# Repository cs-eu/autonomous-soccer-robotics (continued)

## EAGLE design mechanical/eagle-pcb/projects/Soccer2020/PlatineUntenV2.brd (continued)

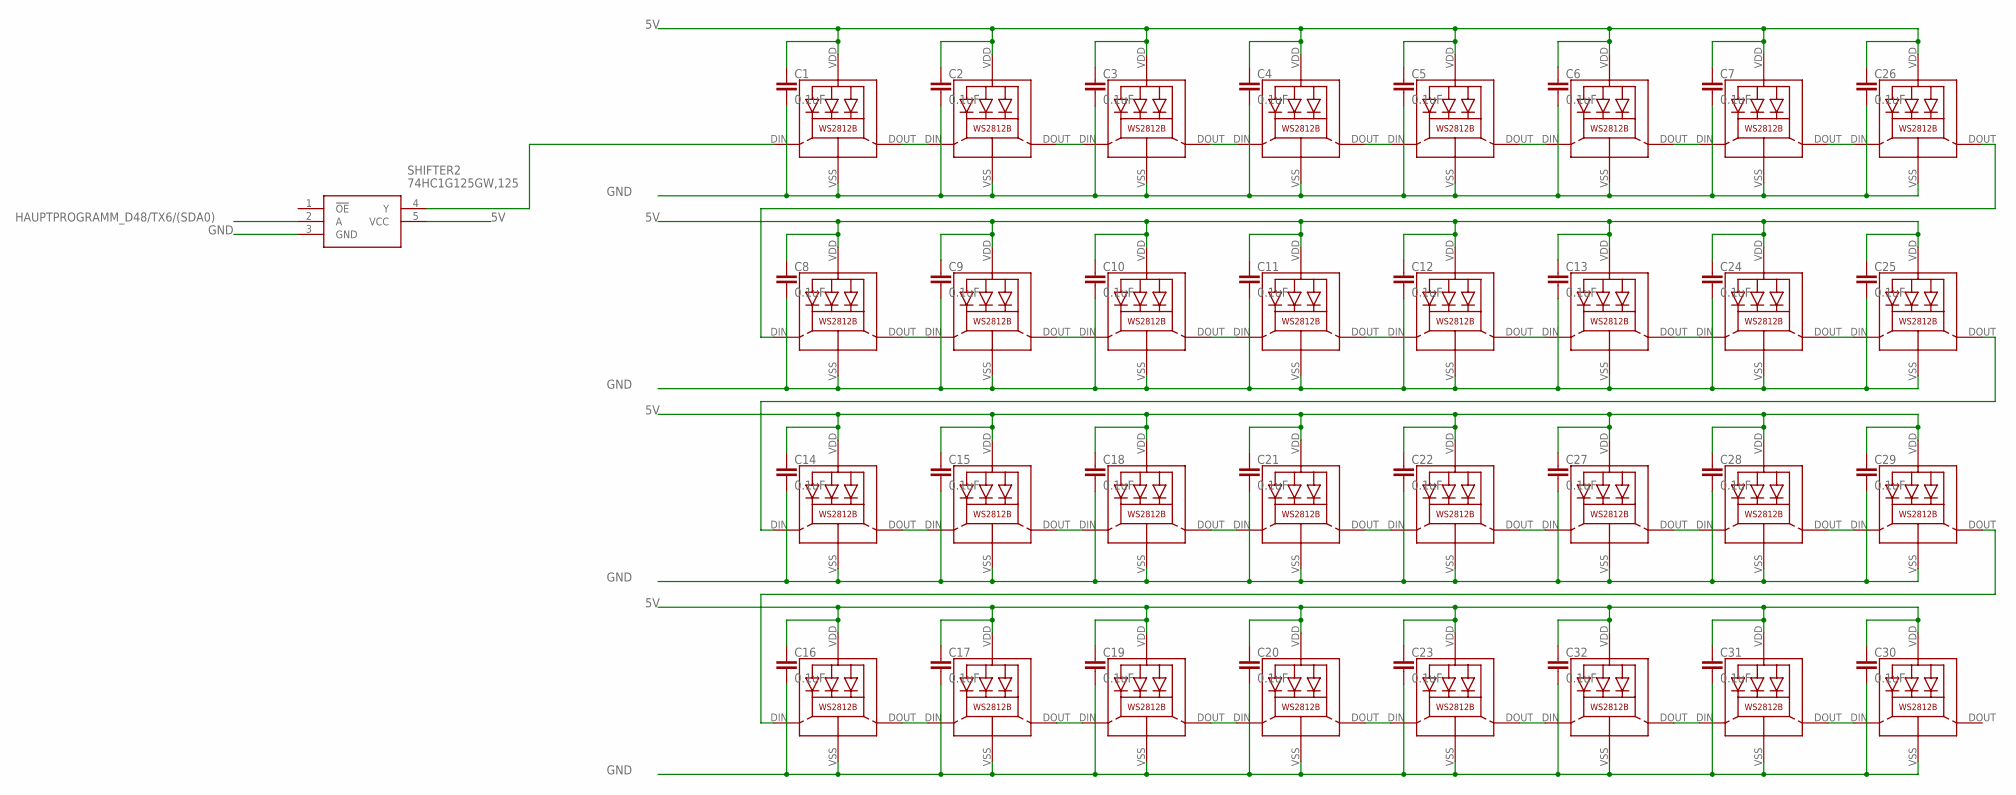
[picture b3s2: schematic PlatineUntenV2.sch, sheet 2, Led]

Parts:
C1, C2, C3, C4, C5, C6, C7, C8, C9, C10, C11, C12, C13, C14, C15, C16, C17, C18, C19, C20, C21, C22, C23, C24, C25, C26, C27, C28, C29, C30, C31, C32: 0.1uF; C0805
LED33, LED34, LED35, LED36, LED37, LED38, LED39, LED40, LED41, LED42, LED43, LED44, LED45, LED46, LED47, LED48, LED49, LED50, LED51, LED52, LED53, LED54, LED55, LED56, LED57, LED58, LED59, LED60, LED61, LED62, LED63, LED64: WS2812B
SHIFTER2: 74HC1G125GW,125; SOT65P212X110-5N

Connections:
5V: C1.1, C2.1, C3.1, C4.1, C5.1, C6.1, C7.1, C8.1, C9.1, C10.1, C11.1, C12.1, C13.1, C14.1, C15.1, C16.1, C17.1, C18.1, C19.1, C20.1, C21.1, C22.1, C23.1, C24.1, C25.1, C26.1, C27.1, C28.1, C29.1, C30.1, C31.1, C32.1, LED33.VDD, LED34.VDD, LED35.VDD, LED36.VDD, LED37.VDD, LED38.VDD, LED39.VDD, LED40.VDD, LED41.VDD, LED42.VDD, LED43.VDD, LED44.VDD, LED45.VDD, LED46.VDD, LED47.VDD, LED48.VDD, LED49.VDD, LED50.VDD, LED51.VDD, LED52.VDD, LED53.VDD, LED54.VDD, LED55.VDD, LED56.VDD, LED57.VDD, LED58.VDD, LED59.VDD, LED60.VDD, LED61.VDD, LED62.VDD, LED63.VDD, LED64.VDD, SHIFTER2.5 (VCC); also elsewhere on the board
GND: C1.2, C2.2, C3.2, C4.2, C5.2, C6.2, C7.2, C8.2, C9.2, C10.2, C11.2, C12.2, C13.2, C14.2, C15.2, C16.2, C17.2, C18.2, C19.2, C20.2, C21.2, C22.2, C23.2, C24.2, C25.2, C26.2, C27.2, C28.2, C29.2, C30.2, C31.2, C32.2, LED33.VSS (GND), LED34.VSS (GND), LED35.VSS (GND), LED36.VSS (GND), LED37.VSS (GND), LED38.VSS (GND), LED39.VSS (GND), LED40.VSS (GND), LED41.VSS (GND), LED42.VSS (GND), LED43.VSS (GND), LED44.VSS (GND), LED45.VSS (GND), LED46.VSS (GND), LED47.VSS (GND), LED48.VSS (GND), LED49.VSS (GND), LED50.VSS (GND), LED51.VSS (GND), LED52.VSS (GND), LED53.VSS (GND), LED54.VSS (GND), LED55.VSS (GND), LED56.VSS (GND), LED57.VSS (GND), LED58.VSS (GND), LED59.VSS (GND), LED60.VSS (GND), LED61.VSS (GND), LED62.VSS (GND), LED63.VSS (GND), LED64.VSS (GND), SHIFTER2.3 (GND); also elsewhere on the board
HAUPTPROGRAMM_D48/TX6/(SDA0): SHIFTER2.2 (A); also elsewhere on the board
unnamed: LED33.DIN (DI), SHIFTER2.4 (Y)
unnamed: LED33.DOUT (DO), LED34.DIN (DI)
unnamed: LED34.DOUT (DO), LED35.DIN (DI)
unnamed: LED35.DOUT (DO), LED36.DIN (DI)
unnamed: LED36.DOUT (DO), LED37.DIN (DI)
unnamed: LED37.DOUT (DO), LED38.DIN (DI)
unnamed: LED38.DOUT (DO), LED39.DIN (DI)
unnamed: LED39.DOUT (DO), LED40.DIN (DI)
unnamed: LED40.DOUT (DO), LED41.DIN (DI)
unnamed: LED41.DOUT (DO), LED42.DIN (DI)
unnamed: LED42.DOUT (DO), LED43.DIN (DI)
unnamed: LED43.DOUT (DO), LED44.DIN (DI)
unnamed: LED44.DOUT (DO), LED45.DIN (DI)
unnamed: LED45.DOUT (DO), LED46.DIN (DI)
unnamed: LED46.DOUT (DO), LED47.DIN (DI)
unnamed: LED47.DOUT (DO), LED48.DIN (DI)
unnamed: LED48.DOUT (DO), LED49.DIN (DI)
unnamed: LED49.DOUT (DO), LED50.DIN (DI)
unnamed: LED50.DOUT (DO), LED51.DIN (DI)
unnamed: LED51.DOUT (DO), LED52.DIN (DI)
unnamed: LED52.DOUT (DO), LED53.DIN (DI)
unnamed: LED53.DOUT (DO), LED54.DIN (DI)
unnamed: LED54.DOUT (DO), LED55.DIN (DI)
unnamed: LED55.DOUT (DO), LED56.DIN (DI)
unnamed: LED56.DOUT (DO), LED57.DIN (DI)
unnamed: LED57.DOUT (DO), LED58.DIN (DI)
unnamed: LED58.DOUT (DO), LED59.DIN (DI)
unnamed: LED59.DOUT (DO), LED60.DIN (DI)
unnamed: LED60.DOUT (DO), LED61.DIN (DI)
unnamed: LED61.DOUT (DO), LED62.DIN (DI)
unnamed: LED62.DOUT (DO), LED63.DIN (DI)
unnamed: LED63.DOUT (DO), LED64.DIN (DI)

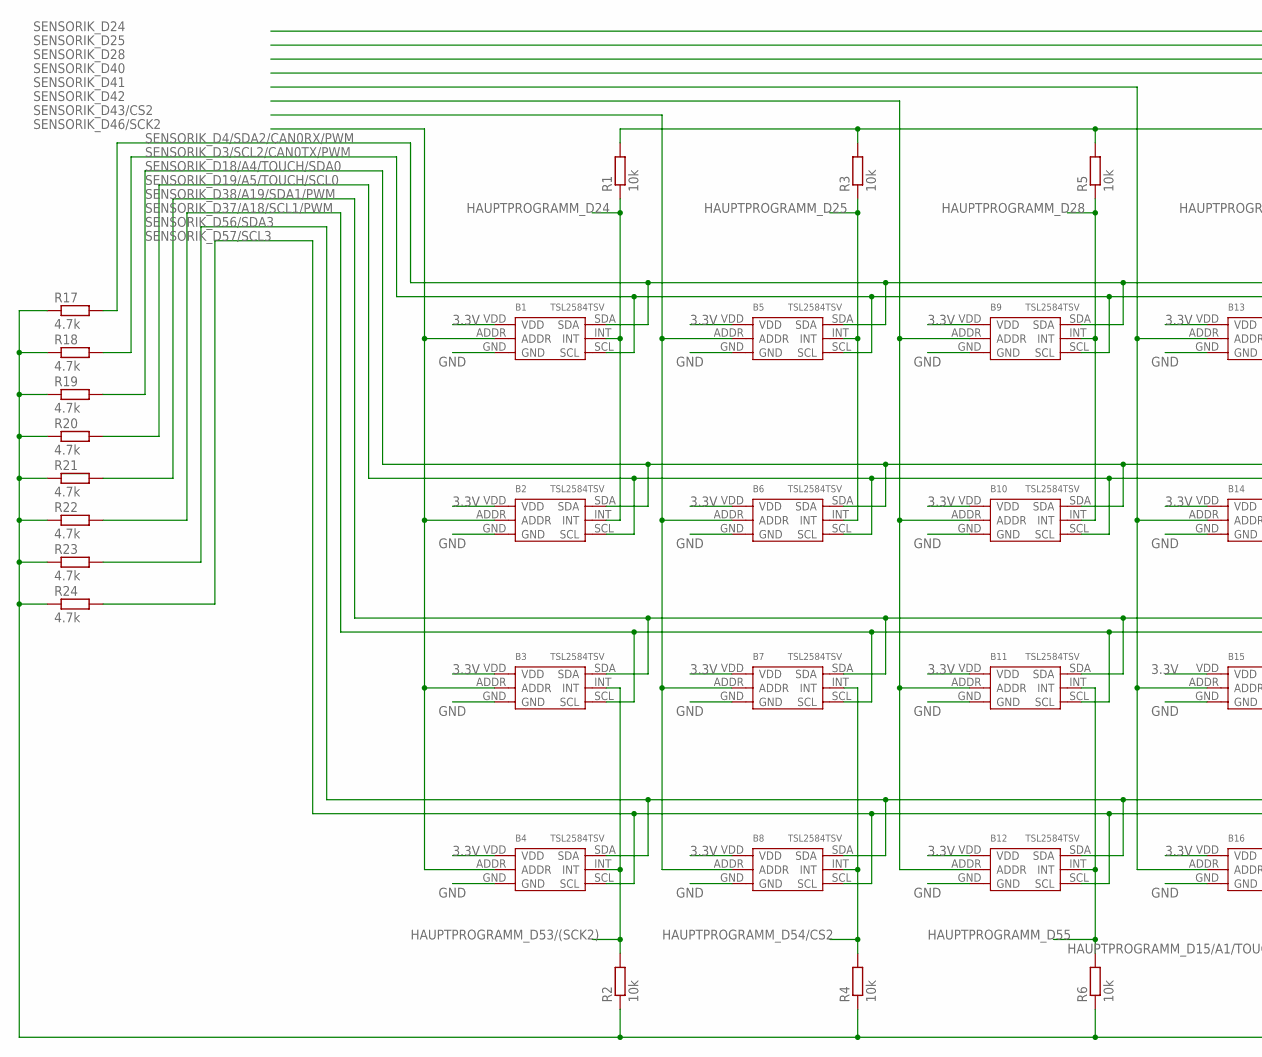
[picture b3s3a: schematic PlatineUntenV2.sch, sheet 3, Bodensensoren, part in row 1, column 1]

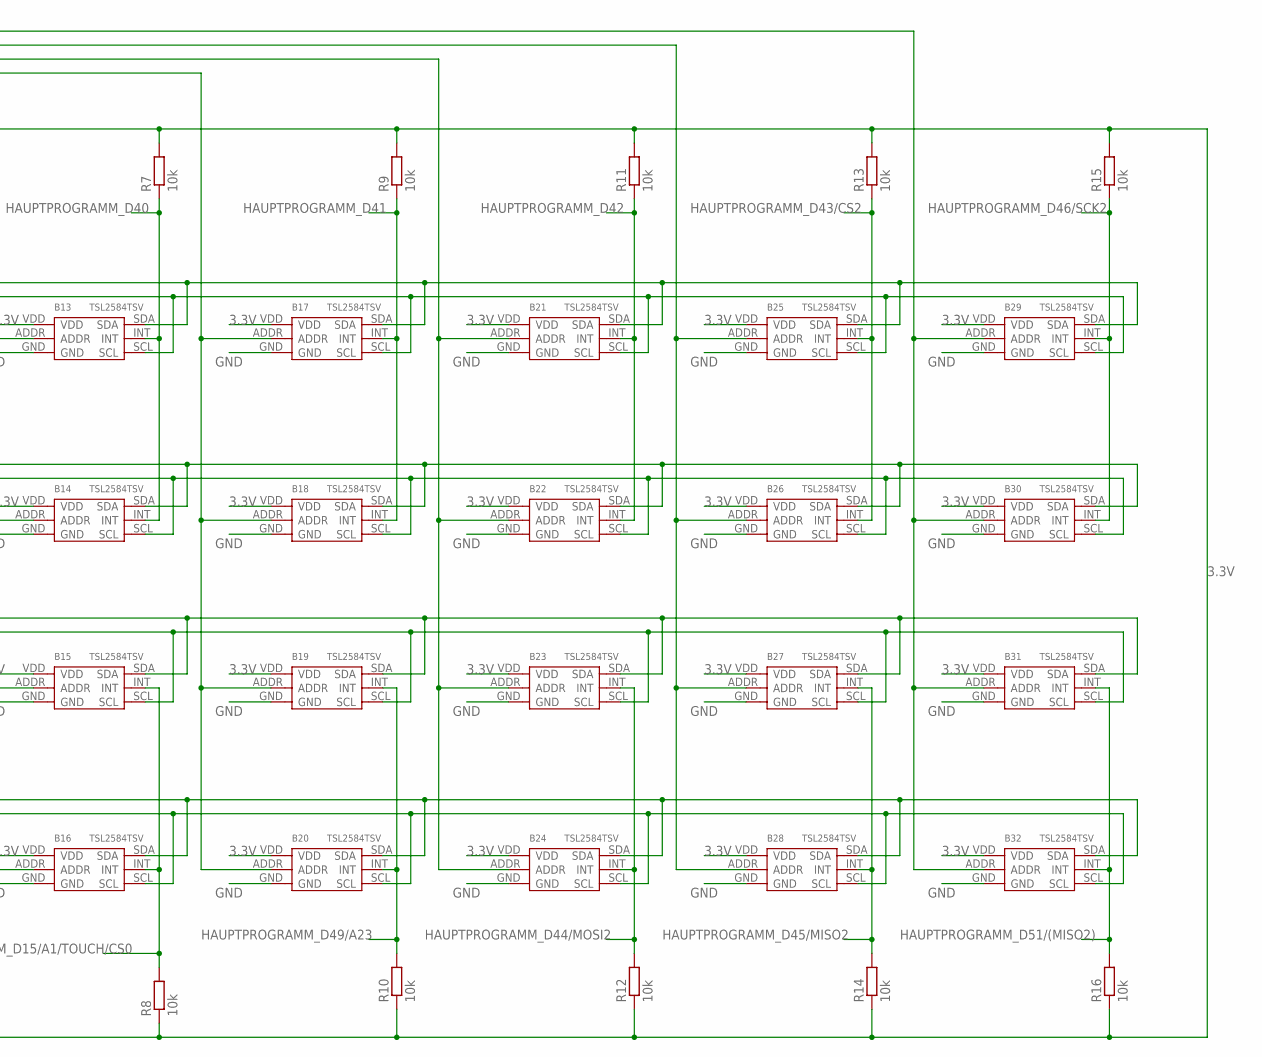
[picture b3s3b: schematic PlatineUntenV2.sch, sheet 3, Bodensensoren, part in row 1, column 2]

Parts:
B1, B2, B3, B4, B5, B6, B7, B8, B9, B10, B11, B12, B13, B14, B15, B16, B17, B18, B19, B20, B21, B22, B23, B24, B25, B26, B27, B28, B29, B30, B31, B32: TSL2584TSV
R1, R2, R3, R4, R5, R6, R7, R8, R9, R10, R11, R12, R13, R14, R15, R16: 10k; R0805
R17, R18, R19, R20, R21, R22, R23, R24: 4.7k; R0805

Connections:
3.3V: B1.VDD, B2.VDD, B3.VDD, B4.VDD, B5.VDD, B6.VDD, B7.VDD, B8.VDD, B9.VDD, B10.VDD, B11.VDD, B12.VDD, B13.VDD, B14.VDD, B15.VDD, B16.VDD, B17.VDD, B18.VDD, B19.VDD, B20.VDD, B21.VDD, B22.VDD, B23.VDD, B24.VDD, B25.VDD, B26.VDD, B27.VDD, B28.VDD, B29.VDD, B30.VDD, B31.VDD, B32.VDD, R1.2, R2.1, R3.2, R4.1, R5.2, R6.1, R7.2, R8.1, R9.2, R10.1, R11.2, R12.1, R13.2, R14.1, R15.2, R16.1, R17.1, R18.1, R19.1, R20.1, R21.1, R22.1, R23.1, R24.1; also elsewhere on the board
GND: B1.GND, B2.GND, B3.GND, B4.GND, B5.GND, B6.GND, B7.GND, B8.GND, B9.GND, B10.GND, B11.GND, B12.GND, B13.GND, B14.GND, B15.GND, B16.GND, B17.GND, B18.GND, B19.GND, B20.GND, B21.GND, B22.GND, B23.GND, B24.GND, B25.GND, B26.GND, B27.GND, B28.GND, B29.GND, B30.GND, B31.GND, B32.GND; also elsewhere on the board
HAUPTPROGRAMM_D15/A1/TOUCH/CS0: B15.INT, B16.INT, R8.2; also elsewhere on the board
HAUPTPROGRAMM_D24: B1.INT, B2.INT, R1.1; also elsewhere on the board
HAUPTPROGRAMM_D25: B5.INT, B6.INT, R3.1; also elsewhere on the board
HAUPTPROGRAMM_D28: B9.INT, B10.INT, R5.1; also elsewhere on the board
HAUPTPROGRAMM_D40: B13.INT, B14.INT, R7.1; also elsewhere on the board
HAUPTPROGRAMM_D41: B17.INT, B18.INT, R9.1; also elsewhere on the board
HAUPTPROGRAMM_D42: B21.INT, B22.INT, R11.1; also elsewhere on the board
HAUPTPROGRAMM_D43/CS2: B25.INT, B26.INT, R13.1; also elsewhere on the board
HAUPTPROGRAMM_D44/MOSI2: B23.INT, B24.INT, R12.2; also elsewhere on the board
HAUPTPROGRAMM_D45/MISO2: B27.INT, B28.INT, R14.2; also elsewhere on the board
HAUPTPROGRAMM_D46/SCK2: B29.INT, B30.INT, R15.1; also elsewhere on the board
HAUPTPROGRAMM_D49/A23: B19.INT, B20.INT, R10.2; also elsewhere on the board
HAUPTPROGRAMM_D51/(MISO2): B31.INT, B32.INT, R16.2; also elsewhere on the board
HAUPTPROGRAMM_D53/(SCK2): B3.INT, B4.INT, R2.2; also elsewhere on the board
HAUPTPROGRAMM_D54/CS2: B7.INT, B8.INT, R4.2; also elsewhere on the board
HAUPTPROGRAMM_D55: B11.INT, B12.INT, R6.2; also elsewhere on the board
SENSORIK_D3/SCL2/CAN0TX/PWM: B1.SCL, B5.SCL, B9.SCL, B13.SCL, B17.SCL, B21.SCL, B25.SCL, B29.SCL, R18.2; also elsewhere on the board
SENSORIK_D4/SDA2/CAN0RX/PWM: B1.SDA, B5.SDA, B9.SDA, B13.SDA, B17.SDA, B21.SDA, B25.SDA, B29.SDA, R17.2; also elsewhere on the board
SENSORIK_D18/A4/TOUCH/SDA0: B2.SDA, B6.SDA, B10.SDA, B14.SDA, B18.SDA, B22.SDA, B26.SDA, B30.SDA, R19.2; also elsewhere on the board
SENSORIK_D19/A5/TOUCH/SCL0: B2.SCL, B6.SCL, B10.SCL, B14.SCL, B18.SCL, B22.SCL, B26.SCL, B30.SCL, R20.2; also elsewhere on the board
SENSORIK_D24: B29.ADDR, B30.ADDR, B31.ADDR, B32.ADDR; also elsewhere on the board
SENSORIK_D25: B25.ADDR, B26.ADDR, B27.ADDR, B28.ADDR; also elsewhere on the board
SENSORIK_D28: B21.ADDR, B22.ADDR, B23.ADDR, B24.ADDR; also elsewhere on the board
SENSORIK_D37/A18/SCL1/PWM: B3.SCL, B7.SCL, B11.SCL, B15.SCL, B19.SCL, B23.SCL, B27.SCL, B31.SCL, R22.2; also elsewhere on the board
SENSORIK_D38/A19/SDA1/PWM: B3.SDA, B7.SDA, B11.SDA, B15.SDA, B19.SDA, B23.SDA, B27.SDA, B31.SDA, R21.2; also elsewhere on the board
SENSORIK_D40: B17.ADDR, B18.ADDR, B19.ADDR, B20.ADDR; also elsewhere on the board
SENSORIK_D41: B13.ADDR, B14.ADDR, B15.ADDR, B16.ADDR; also elsewhere on the board
SENSORIK_D42: B9.ADDR, B10.ADDR, B11.ADDR, B12.ADDR; also elsewhere on the board
SENSORIK_D43/CS2: B5.ADDR, B6.ADDR, B7.ADDR, B8.ADDR; also elsewhere on the board
SENSORIK_D46/SCK2: B1.ADDR, B2.ADDR, B3.ADDR, B4.ADDR; also elsewhere on the board
SENSORIK_D56/SDA3: B4.SDA, B8.SDA, B12.SDA, B16.SDA, B20.SDA, B24.SDA, B28.SDA, B32.SDA, R23.2; also elsewhere on the board
SENSORIK_D57/SCL3: B4.SCL, B8.SCL, B12.SCL, B16.SCL, B20.SCL, B24.SCL, B28.SCL, B32.SCL, R24.2; also elsewhere on the board

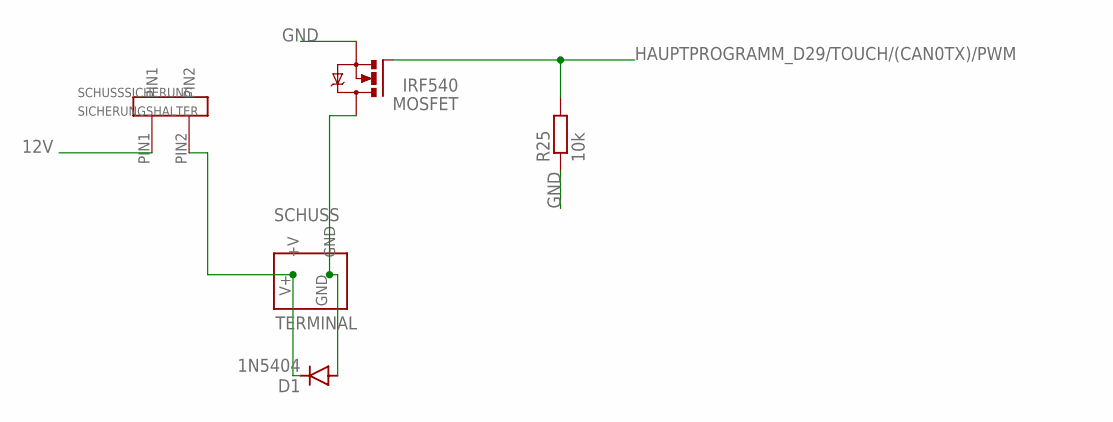
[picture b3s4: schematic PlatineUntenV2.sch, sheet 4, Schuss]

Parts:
D1: 1N5404; DO201-15
MOSFET: IRF540; TO220BV
R25: 10k; R0805
SCHUSS: TERMINAL
SCHUSSSICHERUNG: SICHERUNGSHALTER

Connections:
12V: SCHUSSSICHERUNG.PIN1; also elsewhere on the board
GND: MOSFET.S, R25.1; also elsewhere on the board
HAUPTPROGRAMM_D29/TOUCH/(CAN0TX)/PWM: MOSFET.G, R25.2; also elsewhere on the board
unnamed: D1.A, MOSFET.D, SCHUSS.GND
unnamed: D1.C, SCHUSS.V+ (+V), SCHUSSSICHERUNG.PIN2

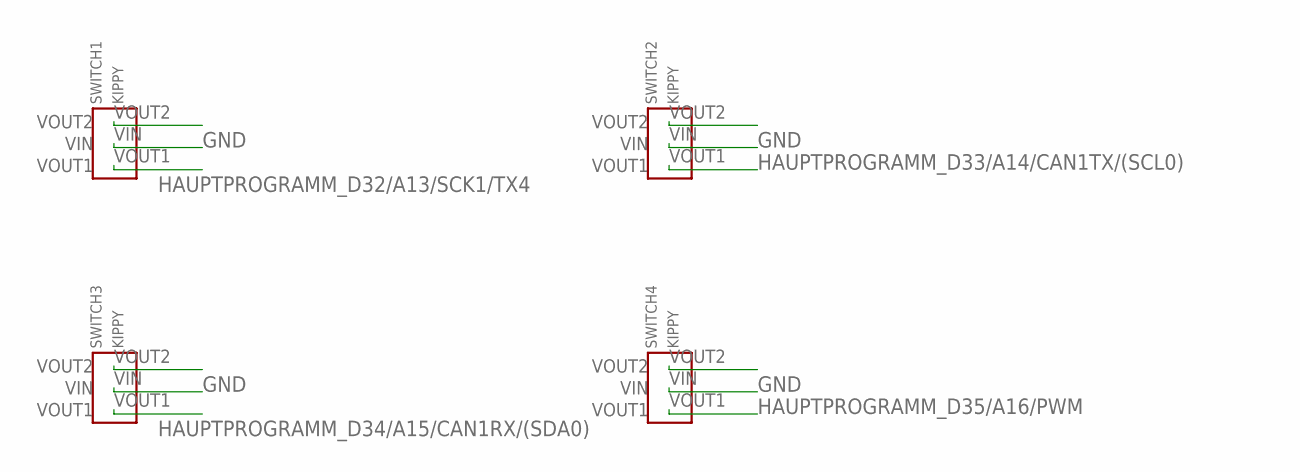
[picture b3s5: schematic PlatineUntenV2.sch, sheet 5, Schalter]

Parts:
SWITCH1, SWITCH2, SWITCH3, SWITCH4: KIPPY

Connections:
GND: SWITCH1.VIN, SWITCH2.VIN, SWITCH3.VIN, SWITCH4.VIN; also elsewhere on the board
HAUPTPROGRAMM_D32/A13/SCK1/TX4: SWITCH1.VOUT1; also elsewhere on the board
HAUPTPROGRAMM_D33/A14/CAN1TX/(SCL0): SWITCH2.VOUT1; also elsewhere on the board
HAUPTPROGRAMM_D34/A15/CAN1RX/(SDA0): SWITCH3.VOUT1; also elsewhere on the board
HAUPTPROGRAMM_D35/A16/PWM: SWITCH4.VOUT1; also elsewhere on the board

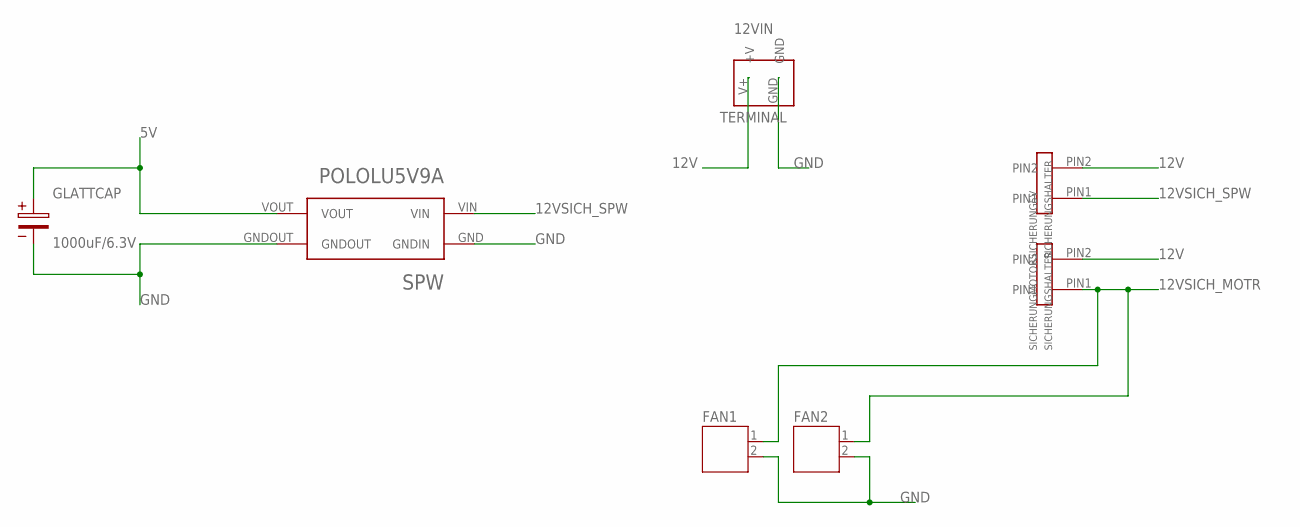
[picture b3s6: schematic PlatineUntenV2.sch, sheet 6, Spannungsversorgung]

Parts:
12VIN: TERMINAL
FAN1, FAN2: JST-PH2
GLATTCAP: 1000uF/6.3V; GLATTCAP
SICHERUNG5V: SICHERUNGSHALTER
SICHERUNGMOTOR: SICHERUNGSHALTER
SPW: POLOLU5V9A

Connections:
5V: GLATTCAP.1, SPW.VOUT; also elsewhere on the board
12V: 12VIN.V+ (+V), SICHERUNG5V.PIN2, SICHERUNGMOTOR.PIN2; also elsewhere on the board
12VSICH_MOTR: FAN1.1, FAN2.1, SICHERUNGMOTOR.PIN1; also elsewhere on the board
12VSICH_SPW: SICHERUNG5V.PIN1, SPW.VIN
GND: 12VIN.GND, FAN1.2, FAN2.2, GLATTCAP.2, SPW.GND (GNDIN), SPW.GNDOUT; also elsewhere on the board

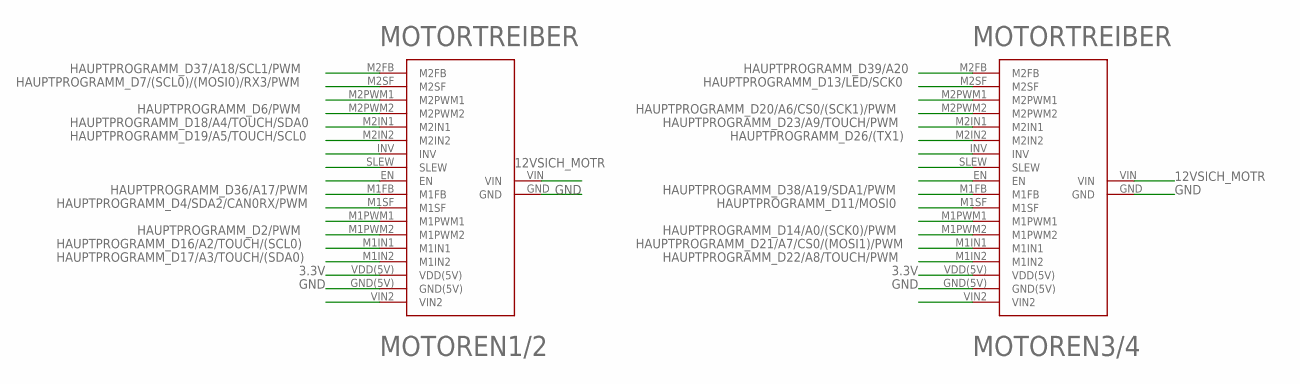
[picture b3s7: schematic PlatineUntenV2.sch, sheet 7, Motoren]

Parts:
MOTOREN1/2, MOTOREN3/4: MOTORTREIBER

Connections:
3.3V: MOTOREN1/2.VDD(5V), MOTOREN3/4.VDD(5V); also elsewhere on the board
12VSICH_MOTR: MOTOREN1/2.VIN, MOTOREN3/4.VIN; also elsewhere on the board
GND: MOTOREN1/2.GND, MOTOREN1/2.GND(5V), MOTOREN3/4.GND, MOTOREN3/4.GND(5V); also elsewhere on the board
HAUPTPROGRAMM_D2/PWM: MOTOREN1/2.M1PWM2; also elsewhere on the board
HAUPTPROGRAMM_D4/SDA2/CAN0RX/PWM: MOTOREN1/2.M1SF; also elsewhere on the board
HAUPTPROGRAMM_D6/PWM: MOTOREN1/2.M2PWM2; also elsewhere on the board
HAUPTPROGRAMM_D7/(SCL0)/(MOSI0)/RX3/PWM: MOTOREN1/2.M2SF; also elsewhere on the board
HAUPTPROGRAMM_D11/MOSI0: MOTOREN3/4.M1SF; also elsewhere on the board
HAUPTPROGRAMM_D13/LED/SCK0: MOTOREN3/4.M2SF; also elsewhere on the board
HAUPTPROGRAMM_D14/A0/(SCK0)/PWM: MOTOREN3/4.M1PWM2; also elsewhere on the board
HAUPTPROGRAMM_D16/A2/TOUCH/(SCL0): MOTOREN1/2.M1IN1; also elsewhere on the board
HAUPTPROGRAMM_D17/A3/TOUCH/(SDA0): MOTOREN1/2.M1IN2; also elsewhere on the board
HAUPTPROGRAMM_D18/A4/TOUCH/SDA0: MOTOREN1/2.M2IN1; also elsewhere on the board
HAUPTPROGRAMM_D19/A5/TOUCH/SCL0: MOTOREN1/2.M2IN2; also elsewhere on the board
HAUPTPROGRAMM_D20/A6/CS0/(SCK1)/PWM: MOTOREN3/4.M2PWM2; also elsewhere on the board
HAUPTPROGRAMM_D21/A7/CS0/(MOSI1)/PWM: MOTOREN3/4.M1IN1; also elsewhere on the board
HAUPTPROGRAMM_D22/A8/TOUCH/PWM: MOTOREN3/4.M1IN2; also elsewhere on the board
HAUPTPROGRAMM_D23/A9/TOUCH/PWM: MOTOREN3/4.M2IN1; also elsewhere on the board
HAUPTPROGRAMM_D26/(TX1): MOTOREN3/4.M2IN2; also elsewhere on the board
HAUPTPROGRAMM_D36/A17/PWM: MOTOREN1/2.M1FB; also elsewhere on the board
HAUPTPROGRAMM_D37/A18/SCL1/PWM: MOTOREN1/2.M2FB; also elsewhere on the board
HAUPTPROGRAMM_D38/A19/SDA1/PWM: MOTOREN3/4.M1FB; also elsewhere on the board
HAUPTPROGRAMM_D39/A20: MOTOREN3/4.M2FB; also elsewhere on the board

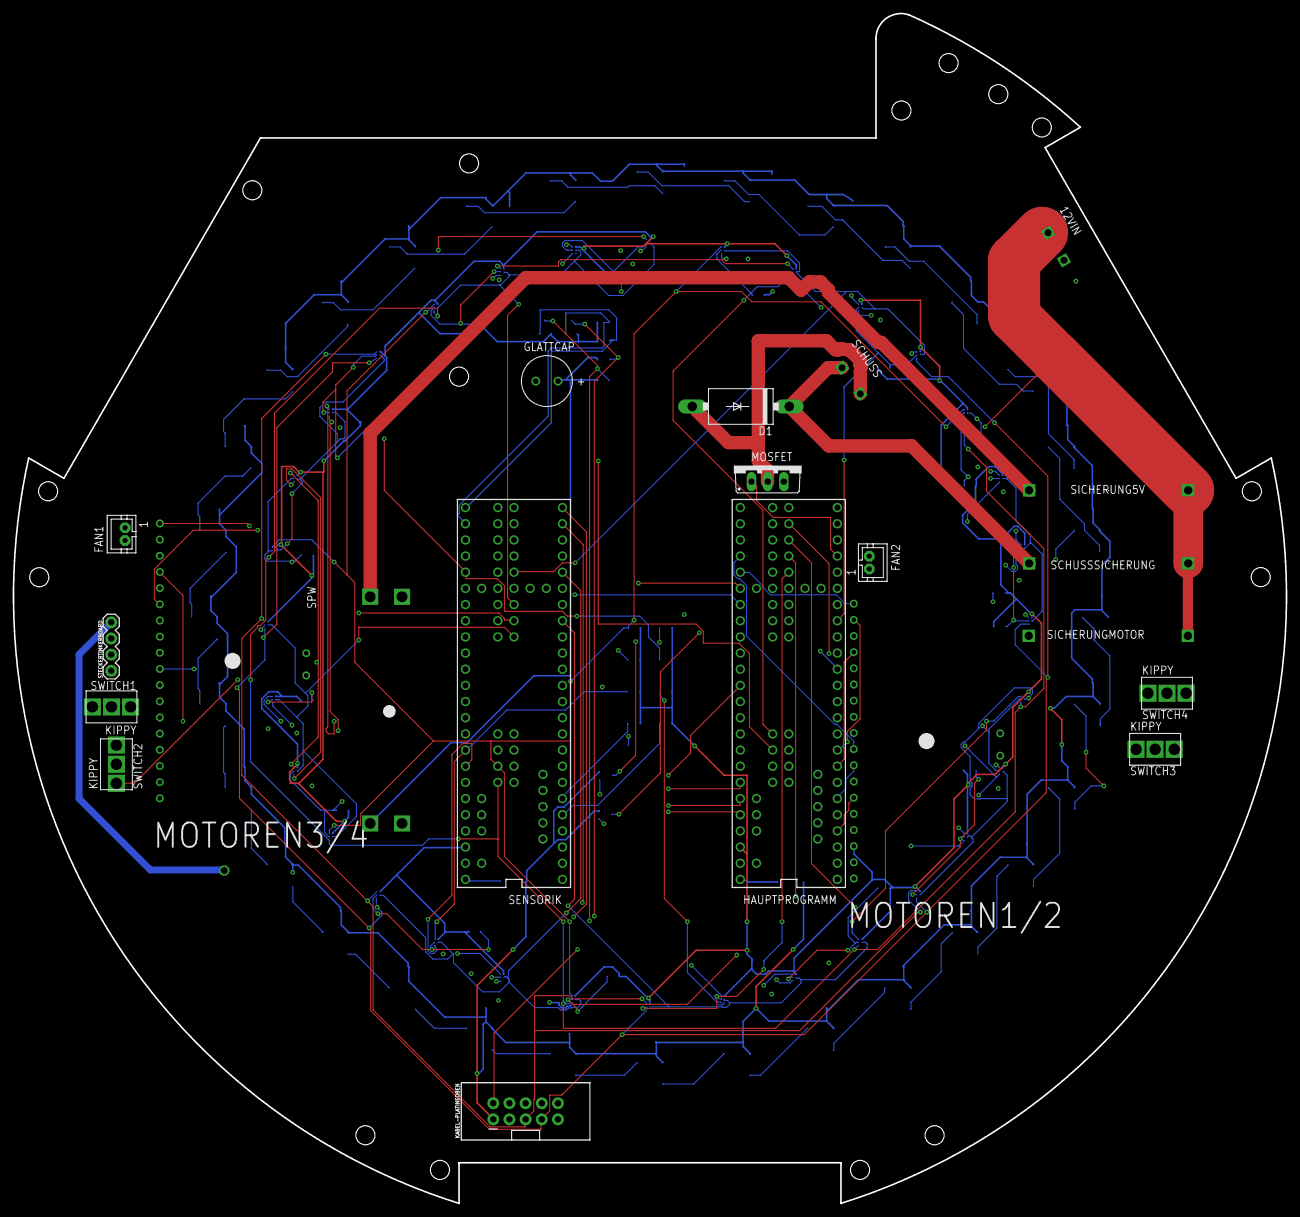
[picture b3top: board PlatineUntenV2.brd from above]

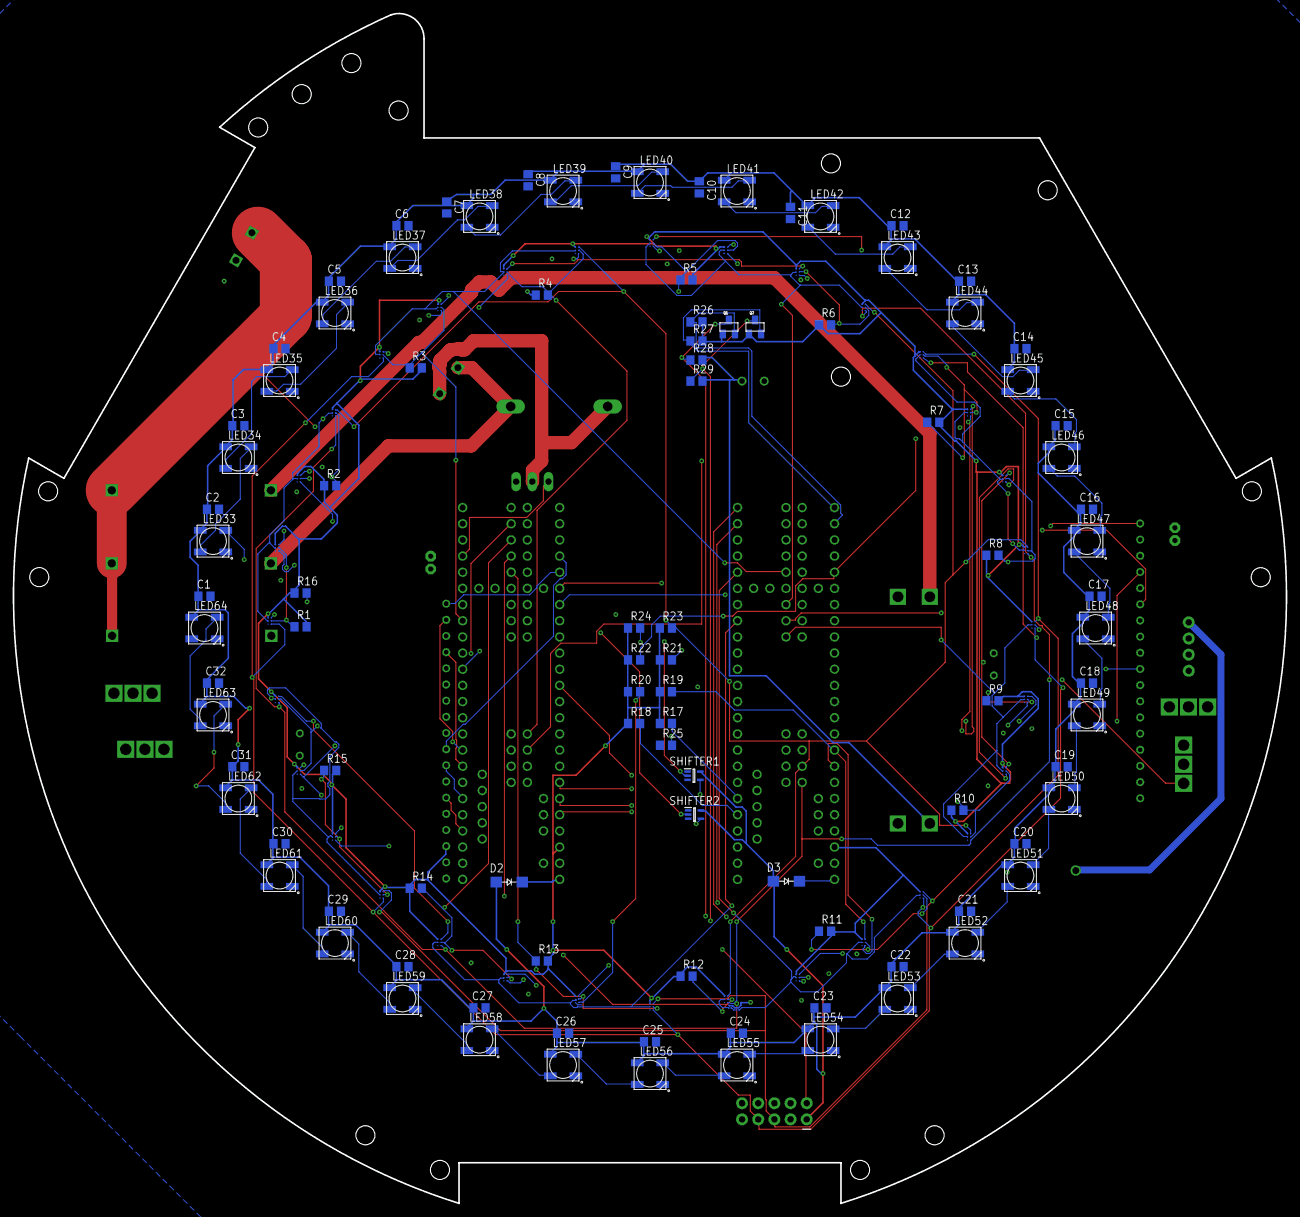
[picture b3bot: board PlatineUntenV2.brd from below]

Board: 4 copper layers, 200.0 x 186.9 mm, 152 parts (131 on the bottom side), 113 nets.

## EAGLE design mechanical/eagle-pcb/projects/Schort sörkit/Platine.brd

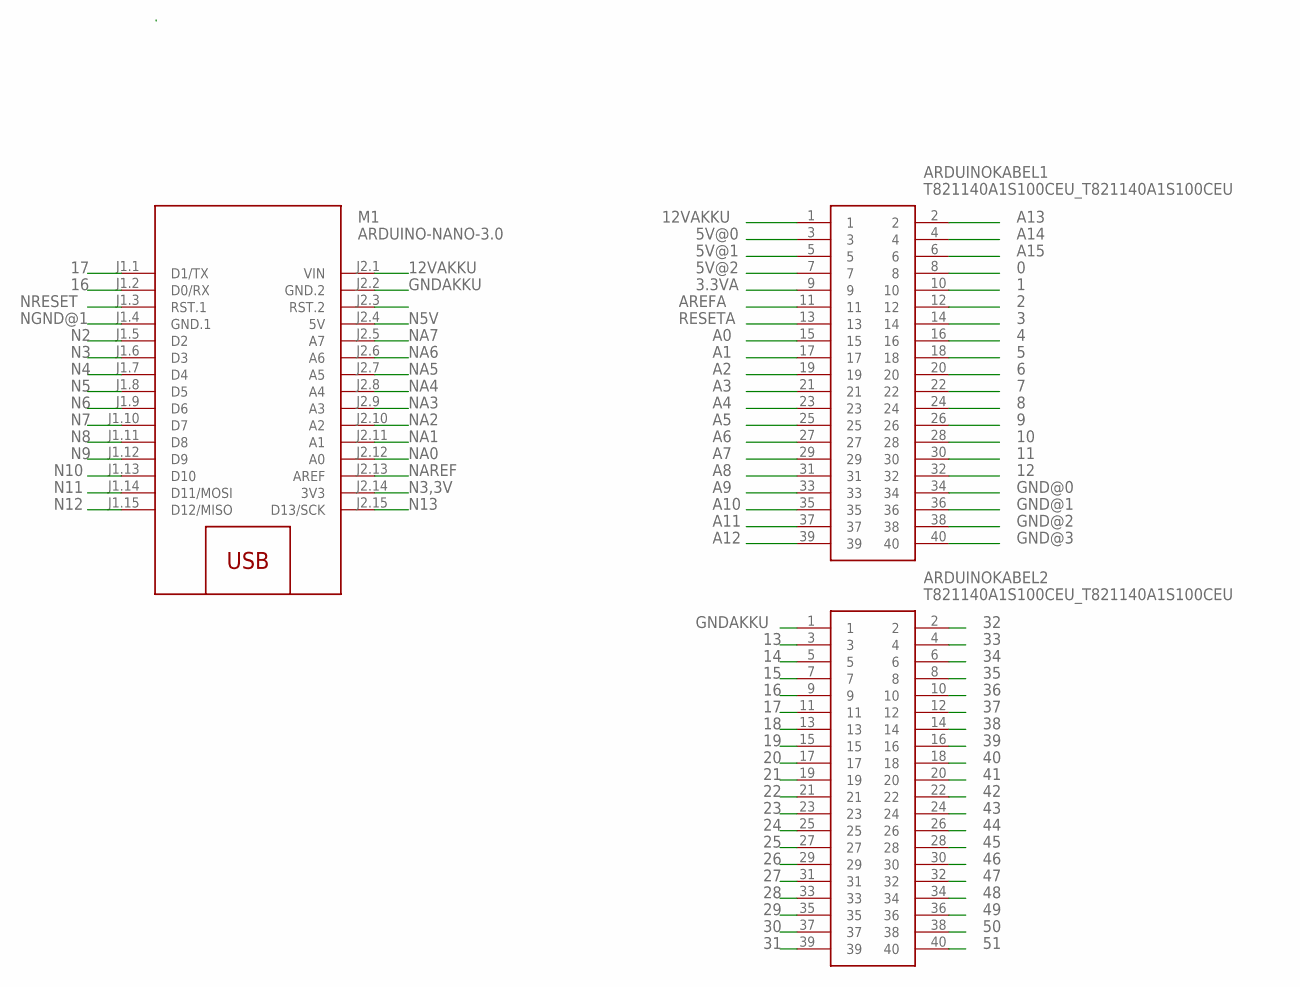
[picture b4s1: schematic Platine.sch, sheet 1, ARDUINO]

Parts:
ARDUINOKABEL1, ARDUINOKABEL2: T821140A1S100CEU_T821140A1S100CEU; T821140A1S100CEU_SHDR40W64P254X254_2X20_5842X89
M1: ARDUINO-NANO-3.0

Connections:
0: ARDUINOKABEL1.8
1: ARDUINOKABEL1.10
2: ARDUINOKABEL1.12; also elsewhere on the board
3: ARDUINOKABEL1.14; also elsewhere on the board
3.3VA: ARDUINOKABEL1.9
4: ARDUINOKABEL1.16; also elsewhere on the board
5: ARDUINOKABEL1.18; also elsewhere on the board
5V@0: ARDUINOKABEL1.3; also elsewhere on the board
5V@1: ARDUINOKABEL1.5
5V@2: ARDUINOKABEL1.7; also elsewhere on the board
6: ARDUINOKABEL1.20; also elsewhere on the board
7: ARDUINOKABEL1.22; also elsewhere on the board
8: ARDUINOKABEL1.24; also elsewhere on the board
9: ARDUINOKABEL1.26
10: ARDUINOKABEL1.28; also elsewhere on the board
11: ARDUINOKABEL1.30; also elsewhere on the board
12: ARDUINOKABEL1.32; also elsewhere on the board
12VAKKU: ARDUINOKABEL1.1, M1.J2.1 (VIN); also elsewhere on the board
13: ARDUINOKABEL2.3; also elsewhere on the board
14: ARDUINOKABEL2.5
15: ARDUINOKABEL2.7
16: ARDUINOKABEL2.9, M1.J1.2 (D0/RX)
17: ARDUINOKABEL2.11, M1.J1.1 (D1/TX)
18: ARDUINOKABEL2.13; also elsewhere on the board
19: ARDUINOKABEL2.15; also elsewhere on the board
20: ARDUINOKABEL2.17
21: ARDUINOKABEL2.19
22: ARDUINOKABEL2.21
23: ARDUINOKABEL2.23
24: ARDUINOKABEL2.25
25: ARDUINOKABEL2.27
26: ARDUINOKABEL2.29
27: ARDUINOKABEL2.31
28: ARDUINOKABEL2.33; also elsewhere on the board
29: ARDUINOKABEL2.35; also elsewhere on the board
30: ARDUINOKABEL2.37; also elsewhere on the board
31: ARDUINOKABEL2.39; also elsewhere on the board
32: ARDUINOKABEL2.2; also elsewhere on the board
33: ARDUINOKABEL2.4; also elsewhere on the board
34: ARDUINOKABEL2.6; also elsewhere on the board
35: ARDUINOKABEL2.8; also elsewhere on the board
36: ARDUINOKABEL2.10; also elsewhere on the board
37: ARDUINOKABEL2.12; also elsewhere on the board
38: ARDUINOKABEL2.14; also elsewhere on the board
39: ARDUINOKABEL2.16; also elsewhere on the board
40: ARDUINOKABEL2.18; also elsewhere on the board
41: ARDUINOKABEL2.20; also elsewhere on the board
42: ARDUINOKABEL2.22; also elsewhere on the board
43: ARDUINOKABEL2.24; also elsewhere on the board
44: ARDUINOKABEL2.26; also elsewhere on the board
45: ARDUINOKABEL2.28; also elsewhere on the board
46: ARDUINOKABEL2.30; also elsewhere on the board
47: ARDUINOKABEL2.32; also elsewhere on the board
48: ARDUINOKABEL2.34
49: ARDUINOKABEL2.36
50: ARDUINOKABEL2.38
51: ARDUINOKABEL2.40
A0: ARDUINOKABEL1.15
A1: ARDUINOKABEL1.17
A2: ARDUINOKABEL1.19
A3: ARDUINOKABEL1.21
A4: ARDUINOKABEL1.23
A5: ARDUINOKABEL1.25
A6: ARDUINOKABEL1.27
A7: ARDUINOKABEL1.29
A8: ARDUINOKABEL1.31
A9: ARDUINOKABEL1.33
A10: ARDUINOKABEL1.35
A11: ARDUINOKABEL1.37
A12: ARDUINOKABEL1.39
A13: ARDUINOKABEL1.2
A14: ARDUINOKABEL1.4
A15: ARDUINOKABEL1.6
AREFA: ARDUINOKABEL1.11
GND@0: ARDUINOKABEL1.34; also elsewhere on the board
GND@1: ARDUINOKABEL1.36
GND@2: ARDUINOKABEL1.38; also elsewhere on the board
GND@3: ARDUINOKABEL1.40
GNDAKKU: ARDUINOKABEL2.1, M1.J2.2 (GND.2); also elsewhere on the board
N2: M1.J1.5 (D2); also elsewhere on the board
N3: M1.J1.6 (D3); also elsewhere on the board
N3,3V: M1.J2.14 (3V3)
N4: M1.J1.7 (D4); also elsewhere on the board
N5: M1.J1.8 (D5); also elsewhere on the board
N5V: M1.J2.4 (5V)
N6: M1.J1.9 (D6); also elsewhere on the board
N7: M1.J1.10 (D7); also elsewhere on the board
N8: M1.J1.11 (D8); also elsewhere on the board
N9: M1.J1.12 (D9); also elsewhere on the board
N10: M1.J1.13 (D10); also elsewhere on the board
N11: M1.J1.14 (D11/MOSI); also elsewhere on the board
N12: M1.J1.15 (D12/MISO); also elsewhere on the board
N13: M1.J2.15 (D13/SCK)
NA0: M1.J2.12 (A0)
NA1: M1.J2.11 (A1)
NA2: M1.J2.10 (A2)
NA3: M1.J2.9 (A3)
NA4: M1.J2.8 (A4)
NA5: M1.J2.7 (A5)
NA6: M1.J2.6 (A6)
NA7: M1.J2.5 (A7)
NAREF: M1.J2.13 (AREF)
NGND@1: M1.J1.4 (GND.1)
NRESET: M1.J1.3 (RST.1)
RESETA: ARDUINOKABEL1.13

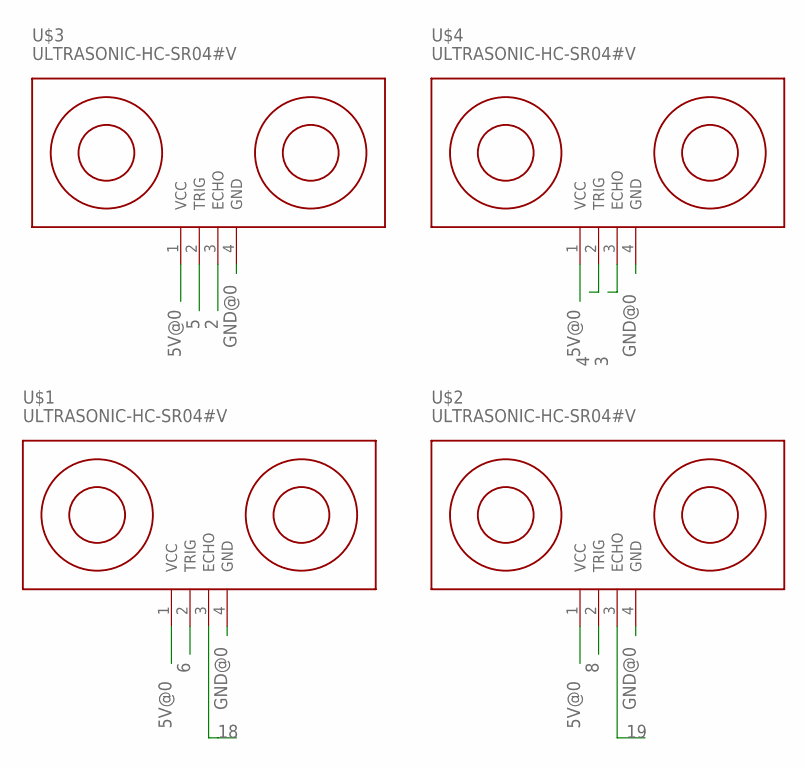
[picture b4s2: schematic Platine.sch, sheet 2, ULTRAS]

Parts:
U$1, U$2, U$3, U$4: ULTRASONIC-HC-SR04#V

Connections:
2: U$3.3 (ECHO); also elsewhere on the board
3: U$4.3 (ECHO); also elsewhere on the board
4: U$4.2 (TRIG); also elsewhere on the board
5: U$3.2 (TRIG); also elsewhere on the board
5V@0: U$1.1 (VCC), U$2.1 (VCC), U$3.1 (VCC), U$4.1 (VCC); also elsewhere on the board
6: U$1.2 (TRIG); also elsewhere on the board
8: U$2.2 (TRIG); also elsewhere on the board
18: U$1.3 (ECHO); also elsewhere on the board
19: U$2.3 (ECHO); also elsewhere on the board
GND@0: U$1.4 (GND), U$2.4 (GND), U$3.4 (GND), U$4.4 (GND); also elsewhere on the board

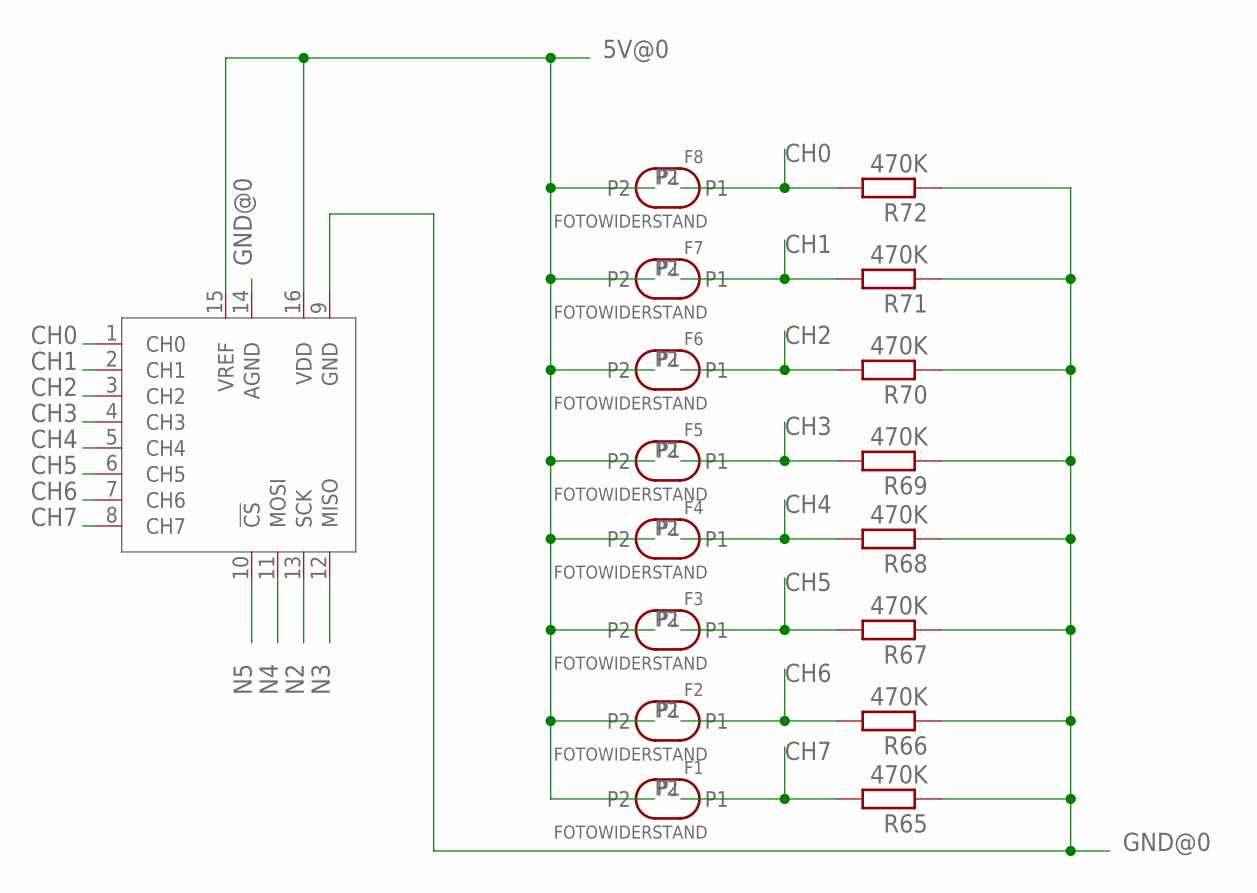
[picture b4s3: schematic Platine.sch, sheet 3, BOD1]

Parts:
F1, F2, F3, F4, F5, F6, F7, F8: FOTOWIDERSTAND
R65, R66, R67, R68, R69, R70, R71, R72: 470K; 0207/7
U$6: MCP3008P; DIL16

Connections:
5V@0: F1.P2, F2.P2, F3.P2, F4.P2, F5.P2, F6.P2, F7.P2, F8.P2, U$6.15 (VREF), U$6.16 (VDD); also elsewhere on the board
CH0: F8.P1, R72.2, U$6.1 (CH0)
CH1: F7.P1, R71.2, U$6.2 (CH1)
CH2: F6.P1, R70.2, U$6.3 (CH2)
CH3: F5.P1, R69.2, U$6.4 (CH3)
CH4: F4.P1, R68.2, U$6.5 (CH4)
CH5: F3.P1, R67.2, U$6.6 (CH5)
CH6: F2.P1, R66.2, U$6.7 (CH6)
CH7: F1.P1, R65.2, U$6.8 (CH7)
GND@0: R65.1, R66.1, R67.1, R68.1, R69.1, R70.1, R71.1, R72.1, U$6.9 (GND), U$6.14 (AGND); also elsewhere on the board
N2: U$6.13 (SCK); also elsewhere on the board
N3: U$6.12 (MISO); also elsewhere on the board
N4: U$6.11 (MOSI); also elsewhere on the board
N5: U$6.10 (!CS); also elsewhere on the board
